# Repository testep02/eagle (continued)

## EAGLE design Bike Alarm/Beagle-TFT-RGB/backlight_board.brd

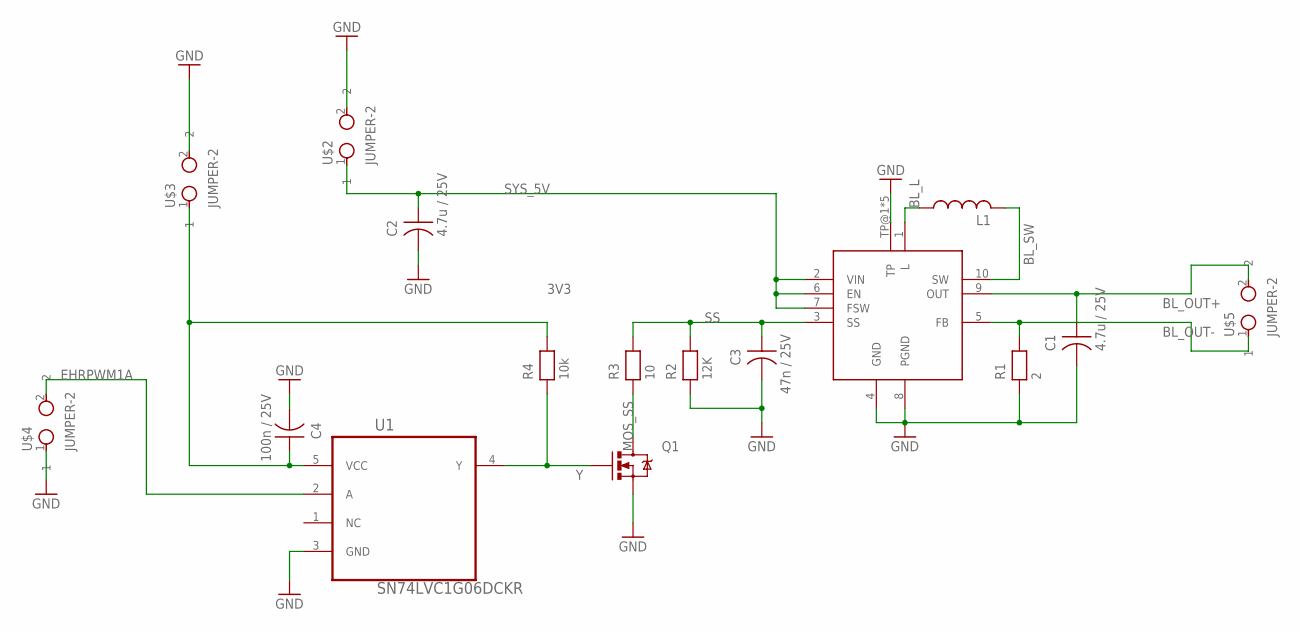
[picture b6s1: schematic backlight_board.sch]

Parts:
C1, C2: 4.7u / 25V; R0805
C3: 47n / 25V; R0603
C4: 100n / 25V; R0603
L1: L-US; VLCF4018-2
Q1: MOSFET-NCHANNELBSS138; SOT23
R1: 2; R0603
R2: 12K; R0603
R3: 10; R0603
R4: 10k; R0603
U1: SN74LVC1G06DCKR; SOT65P210X110-5N
U$1: TPS61080; VSON-10
U$2, U$3, U$4, U$5: JUMPER-2; 1X02

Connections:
3V3: C4.P$2, R4.P$2, U1.5 (VCC), U$3.1
BL_L: L1.1, U$1.1 (L)
BL_OUT+: C1.P$2, U$1.9 (OUT), U$5.2
BL_OUT-: R1.P$2, U$1.5 (FB), U$5.1
BL_SW: L1.2, U$1.10 (SW)
EHRPWM1A: U1.2 (A), U$4.2
GND: C1.P$1, C2.P$1, C3.P$1, C4.P$1, Q1.2 (S), R1.P$1, R2.P$1, U1.3 (GND), U$1.4 (GND), U$1.8 (PGND), U$1.TP@1 (TP), U$1.TP@2 (TP), U$1.TP@3 (TP), U$1.TP@4 (TP), U$1.TP@5 (TP), U$2.2, U$3.2, U$4.1
MOS_SS: Q1.3 (D), R3.P$1
SS: C3.P$2, R2.P$2, R3.P$2, U$1.3 (SS)
SYS_5V: C2.P$2, U$1.2 (VIN), U$1.6 (EN), U$1.7 (FSW), U$2.1
Y: Q1.1 (G), R4.P$1, U1.4 (Y)

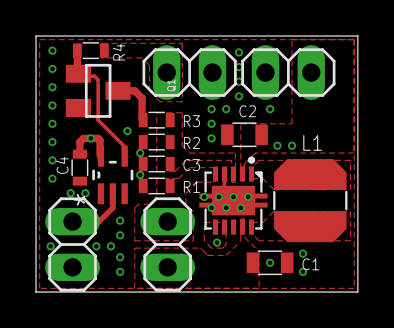
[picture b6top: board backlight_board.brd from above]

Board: 2 copper layers, 17.9 x 14.2 mm, 16 parts (0 on the bottom side), 11 nets.
